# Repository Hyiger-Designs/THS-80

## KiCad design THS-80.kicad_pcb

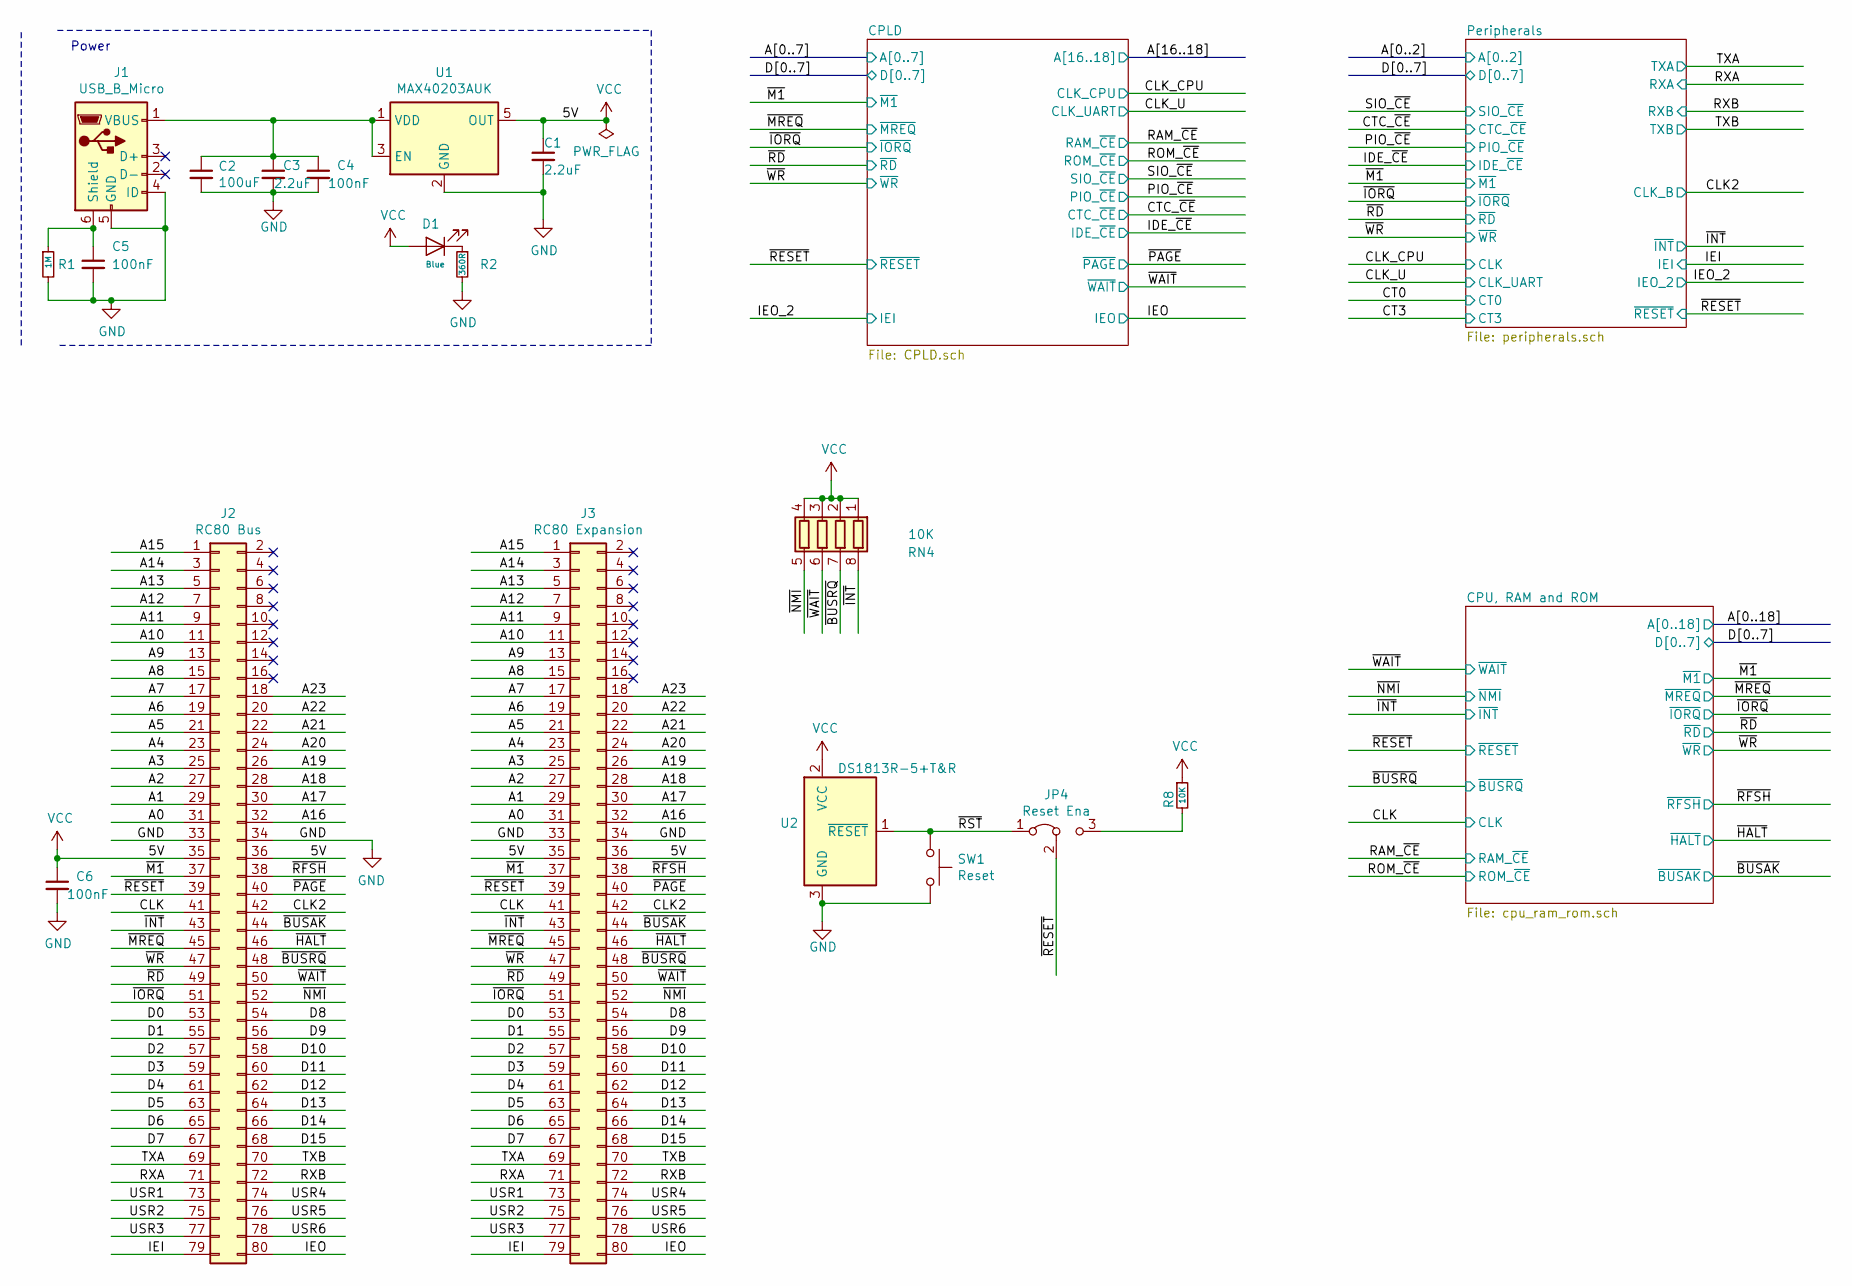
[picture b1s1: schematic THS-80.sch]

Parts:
C1, C3: 2.2uF; C_0603_1608Metric_Pad1.05x0.95mm_HandSolder; MPN C0805C105K4RACTU
C2: 100uF; C_1206_3216Metric_Pad1.42x1.75mm_HandSolder
C4, C5, C6: 100nF; C_0603_1608Metric_Pad1.05x0.95mm_HandSolder; MPN C0805C105K4RACTU
D1: Blue; LED_0603_1608Metric_Pad1.05x0.95mm_HandSolder
J1: USB_B_Micro; USB_Micro-B_Amphenol_10103594-0001LF_Horizontal; MPN 10103594-0001LF
J2: RC80 Bus; PinSocket_2x40_P2.54mm_Vertical
J3: RC80 Expansion; PinSocket_2x40_P2.54mm_Horizontal
JP4: Reset Ena; PinHeader_1x03_P2.54mm_Vertical
R1: 1M; R_0603_1608Metric_Pad1.05x0.95mm_HandSolder
R2: 360R; R_0603_1608Metric_Pad1.05x0.95mm_HandSolder
R8: 10K; R_0603_1608Metric_Pad1.05x0.95mm_HandSolder
RN4: 10K; R_Cat16-4
SW1: Reset; SW_SPST_FSMSM
U1: MAX40203AUK; SOT-23-5_HandSoldering; MPN MAX40203AUK+T; Mouser PN 700-MAX40203AUK+T
U2: DS1813R-5+T&R; SOT-23

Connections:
/A0: J2.31, J3.31; also elsewhere on the board
/A1: J2.29, J3.29; also elsewhere on the board
/A2: J2.27, J3.27; also elsewhere on the board
/A3: J2.25, J3.25; also elsewhere on the board
/A4: J2.23, J3.23; also elsewhere on the board
/A5: J2.21, J3.21; also elsewhere on the board
/A6: J2.19, J3.19; also elsewhere on the board
/A7: J2.17, J3.17; also elsewhere on the board
/A8: J2.15, J3.15; also elsewhere on the board
/A9: J2.13, J3.13; also elsewhere on the board
/A10: J2.11, J3.11; also elsewhere on the board
/A11: J2.9, J3.9; also elsewhere on the board
/A12: J2.7, J3.7; also elsewhere on the board
/A13: J2.5, J3.5; also elsewhere on the board
/A14: J2.3, J3.3; also elsewhere on the board
/A15: J2.1, J3.1; also elsewhere on the board
/A16: J2.32, J3.32; also elsewhere on the board
/A17: J2.30, J3.30; also elsewhere on the board
/A18: J2.28, J3.28; also elsewhere on the board
/A19: J2.26, J3.26
/A20: J2.24, J3.24
/A21: J2.22, J3.22
/A22: J2.20, J3.20
/A23: J2.18, J3.18
/CLK: J2.41, J3.41; also elsewhere on the board
/CLK2: J2.42, J3.42; also elsewhere on the board
/D0: J2.53, J3.53; also elsewhere on the board
/D1: J2.55, J3.55; also elsewhere on the board
/D2: J2.57, J3.57; also elsewhere on the board
/D3: J2.59, J3.59; also elsewhere on the board
/D4: J2.61, J3.61; also elsewhere on the board
/D5: J2.63, J3.63; also elsewhere on the board
/D6: J2.65, J3.65; also elsewhere on the board
/D7: J2.67, J3.67; also elsewhere on the board
/D8: J2.54, J3.54
/D9: J2.56, J3.56
/D10: J2.58, J3.58
/D11: J2.60, J3.60
/D12: J2.62, J3.62
/D13: J2.64, J3.64
/D14: J2.66, J3.66
/D15: J2.68, J3.68
/IEI: J2.79, J3.79; also elsewhere on the board
/IEO: J2.80, J3.80; also elsewhere on the board
/RXA: J2.71, J3.71; also elsewhere on the board
/RXB: J2.72, J3.72; also elsewhere on the board
/TXA: J2.69, J3.69; also elsewhere on the board
/TXB: J2.70, J3.70; also elsewhere on the board
/USR1: J2.73, J3.73
/USR2: J2.75, J3.75
/USR3: J2.77, J3.77
/USR4: J2.74, J3.74
/USR5: J2.76, J3.76
/USR6: J2.78, J3.78
/~BUSAK: J2.44, J3.44; also elsewhere on the board
/~BUSRQ: J2.48, J3.48, RN4.7 (R2.2); also elsewhere on the board
/~HALT: J2.46, J3.46; also elsewhere on the board
/~INT: J2.43, J3.43, RN4.8 (R1.2); also elsewhere on the board
/~IORQ: J2.51, J3.51; also elsewhere on the board
/~M1: J2.37, J3.37; also elsewhere on the board
/~MREQ: J2.45, J3.45; also elsewhere on the board
/~NMI: J2.52, J3.52, RN4.5 (R4.2); also elsewhere on the board
/~PAGE: J2.40, J3.40; also elsewhere on the board
/~RD: J2.49, J3.49; also elsewhere on the board
/~RESET: J2.39, J3.39, JP4.2 (C); also elsewhere on the board
/~RFSH: J2.38, J3.38; also elsewhere on the board
/~RST: JP4.1 (A), SW1.1, U2.1 (~RESET~)
/~WAIT: J2.50, J3.50, RN4.6 (R3.2); also elsewhere on the board
/~WR: J2.47, J3.47; also elsewhere on the board
GND: C1.2, C2.2, C3.2, C4.2, C5.2, C6.2, J1.4 (ID), J1.5 (GND), J2.33, J2.34, J3.33, J3.34, R1.2, R2.2, SW1.2, U1.2 (GND), U2.3 (GND); also elsewhere on the board
unnamed: C2.1, C3.1, C4.1, J1.1 (VBUS), U1.1 (VDD), U1.3 (EN)
unnamed: C5.1, J1.6 (Shield), R1.1
unnamed: D1.1 (K), R2.1
unnamed: JP4.3 (B), R8.2
VCC: C1.1, C6.1, D1.2 (A), J2.35, J2.36, J3.35, J3.36, R8.1, RN4.1 (R1.1), RN4.2 (R2.1), RN4.3 (R3.1), RN4.4 (R4.1), U1.5 (OUT), U2.2 (VCC); also elsewhere on the board

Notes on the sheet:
Power

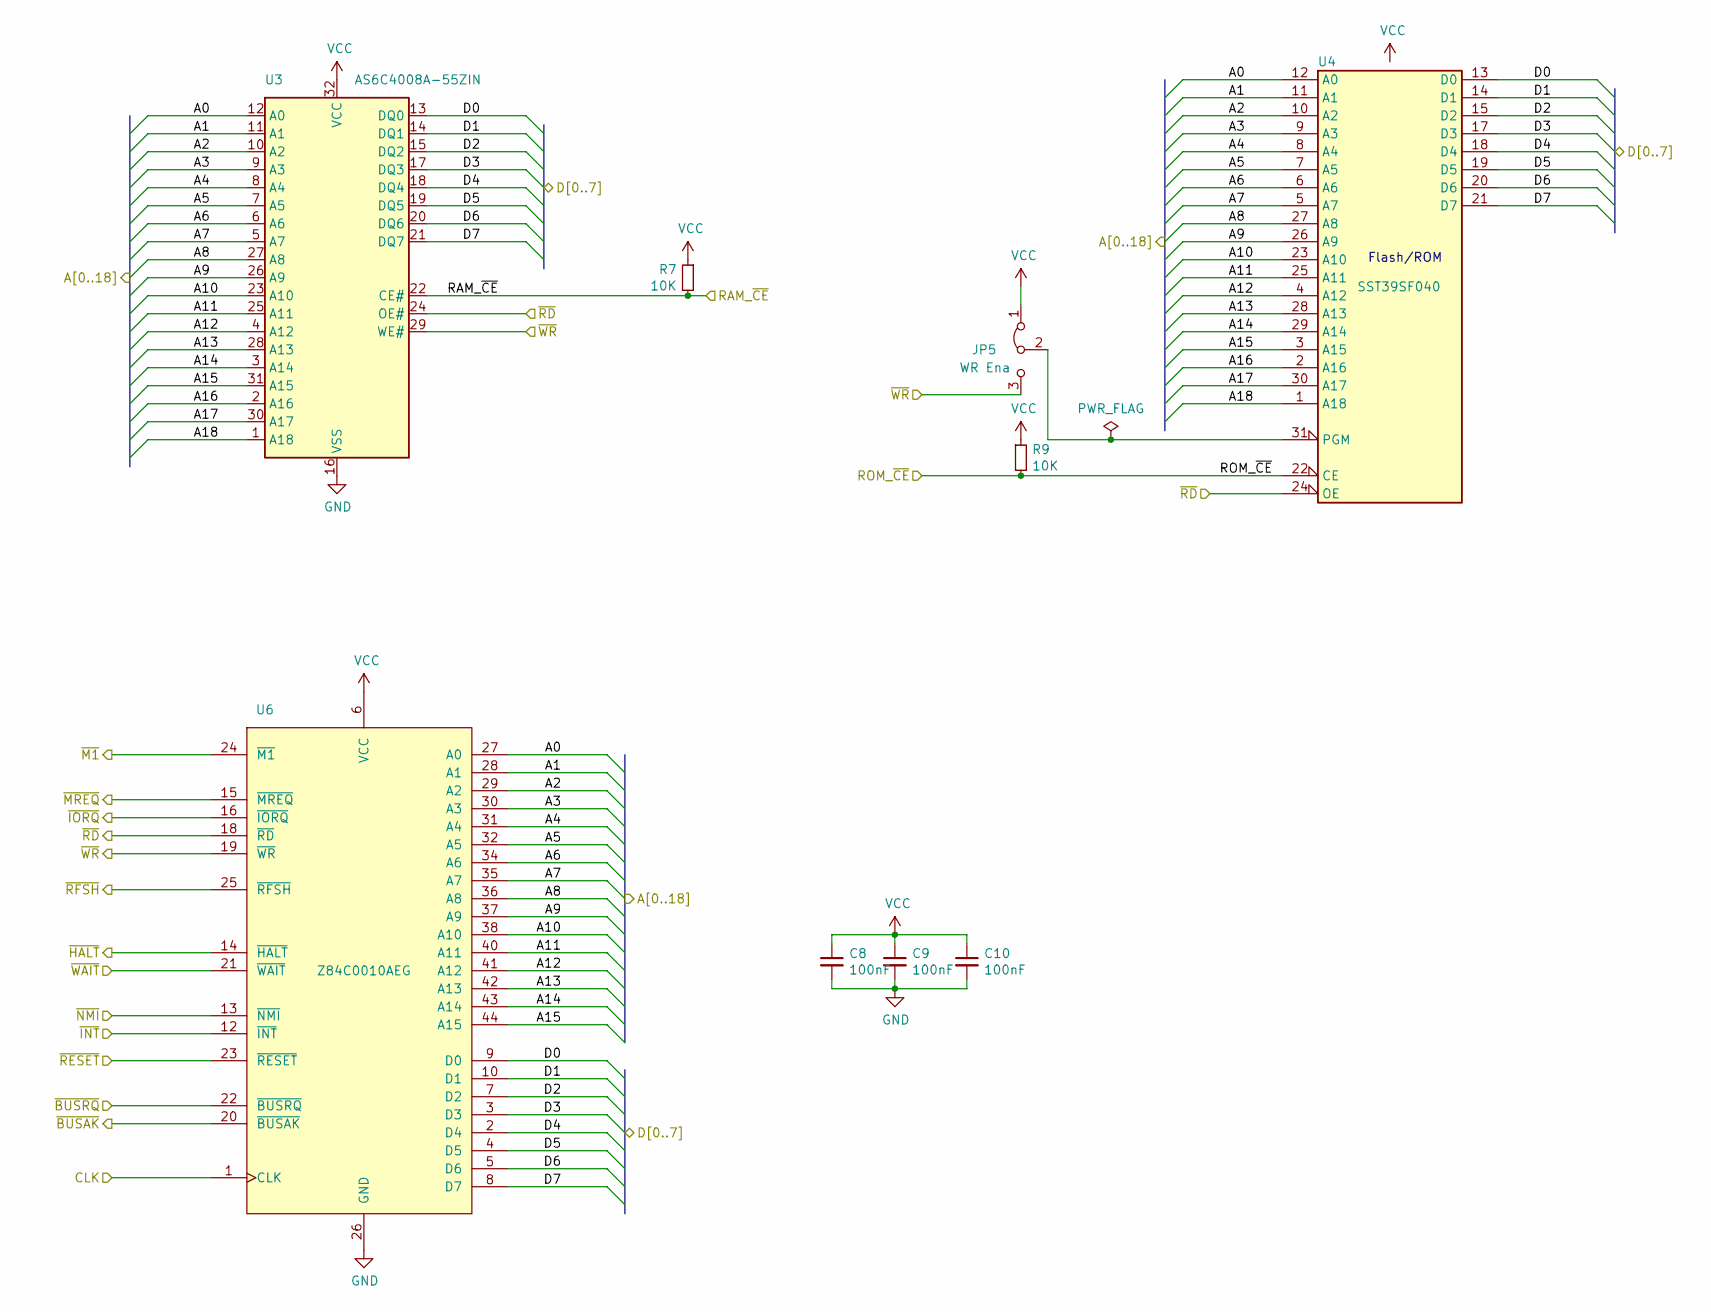
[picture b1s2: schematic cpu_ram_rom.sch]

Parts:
C8, C9, C10: 100nF; C_0603_1608Metric_Pad1.05x0.95mm_HandSolder
JP5: WR Ena; PinHeader_1x03_P2.54mm_Vertical
R7, R9: 10K; R_0603_1608Metric_Pad1.05x0.95mm_HandSolder
U3: AS6C4008A-55ZIN; TSOP-II-32_21.0x10.2mm_P1.27mm
U4: SST39SF040; PLCC-32_11.4x14.0mm_P1.27mm
U6: Z84C0010AEG; LQFP-44_10x10mm_P0.8mm; Manufacturer_Part_Number Z84C0010AEG

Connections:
/A0: U3.12 (A0), U4.12 (A0), U6.27 (A0); also elsewhere on the board
/A1: U3.11 (A1), U4.11 (A1), U6.28 (A1); also elsewhere on the board
/A2: U3.10 (A2), U4.10 (A2), U6.29 (A2); also elsewhere on the board
/A3: U3.9 (A3), U4.9 (A3), U6.30 (A3); also elsewhere on the board
/A4: U3.8 (A4), U4.8 (A4), U6.31 (A4); also elsewhere on the board
/A5: U3.7 (A5), U4.7 (A5), U6.32 (A5); also elsewhere on the board
/A6: U3.6 (A6), U4.6 (A6), U6.34 (A6); also elsewhere on the board
/A7: U3.5 (A7), U4.5 (A7), U6.35 (A7); also elsewhere on the board
/A8: U3.27 (A8), U4.27 (A8), U6.36 (A8); also elsewhere on the board
/A9: U3.26 (A9), U4.26 (A9), U6.37 (A9); also elsewhere on the board
/A10: U3.23 (A10), U4.23 (A10), U6.38 (A10); also elsewhere on the board
/A11: U3.25 (A11), U4.25 (A11), U6.40 (A11); also elsewhere on the board
/A12: U3.4 (A12), U4.4 (A12), U6.41 (A12); also elsewhere on the board
/A13: U3.28 (A13), U4.28 (A13), U6.42 (A13); also elsewhere on the board
/A14: U3.3 (A14), U4.29 (A14), U6.43 (A14); also elsewhere on the board
/A15: U3.31 (A15), U4.3 (A15), U6.44 (A15); also elsewhere on the board
/A16: U3.2 (A16), U4.2 (A16); also elsewhere on the board
/A17: U3.30 (A17), U4.30 (A17); also elsewhere on the board
/A18: U3.1 (A18), U4.1 (A18); also elsewhere on the board
/CLK: U6.1 (CLK); also elsewhere on the board
/D0: U3.13 (DQ0), U4.13 (D0), U6.9 (D0); also elsewhere on the board
/D1: U3.14 (DQ1), U4.14 (D1), U6.10 (D1); also elsewhere on the board
/D2: U3.15 (DQ2), U4.15 (D2), U6.7 (D2); also elsewhere on the board
/D3: U3.17 (DQ3), U4.17 (D3), U6.3 (D3); also elsewhere on the board
/D4: U3.18 (DQ4), U4.18 (D4), U6.2 (D4); also elsewhere on the board
/D5: U3.19 (DQ5), U4.19 (D5), U6.4 (D5); also elsewhere on the board
/D6: U3.20 (DQ6), U4.20 (D6), U6.5 (D6); also elsewhere on the board
/D7: U3.21 (DQ7), U4.21 (D7), U6.8 (D7); also elsewhere on the board
/RAM_~CE: R7.2, U3.22 (CE#); also elsewhere on the board
/ROM_~CE: R9.2, U4.22 (CE); also elsewhere on the board
/~BUSAK: U6.20 (~BUSAK); also elsewhere on the board
/~BUSRQ: U6.22 (~BUSRQ); also elsewhere on the board
/~HALT: U6.14 (~HALT); also elsewhere on the board
/~INT: U6.12 (~INT); also elsewhere on the board
/~IORQ: U6.16 (~IORQ); also elsewhere on the board
/~M1: U6.24 (~M1); also elsewhere on the board
/~MREQ: U6.15 (~MREQ); also elsewhere on the board
/~NMI: U6.13 (~NMI); also elsewhere on the board
/~RD: U3.24 (OE#), U4.24 (OE), U6.18 (~RD); also elsewhere on the board
/~RESET: U6.23 (~RESET); also elsewhere on the board
/~RFSH: U6.25 (~RFSH); also elsewhere on the board
/~WAIT: U6.21 (~WAIT); also elsewhere on the board
/~WR: JP5.3 (B), U3.29 (WE#), U6.19 (~WR); also elsewhere on the board
GND: C8.2, C9.2, C10.2, U3.16 (VSS), U4.16 (GND), U6.26 (GND); also elsewhere on the board
unnamed: JP5.2 (C), U4.31 (PGM)
VCC: C8.1, C9.1, C10.1, JP5.1 (A), R7.1, R9.1, U3.32 (VCC), U4.32 (VCC), U6.6 (VCC); also elsewhere on the board

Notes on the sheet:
Flash/ROM

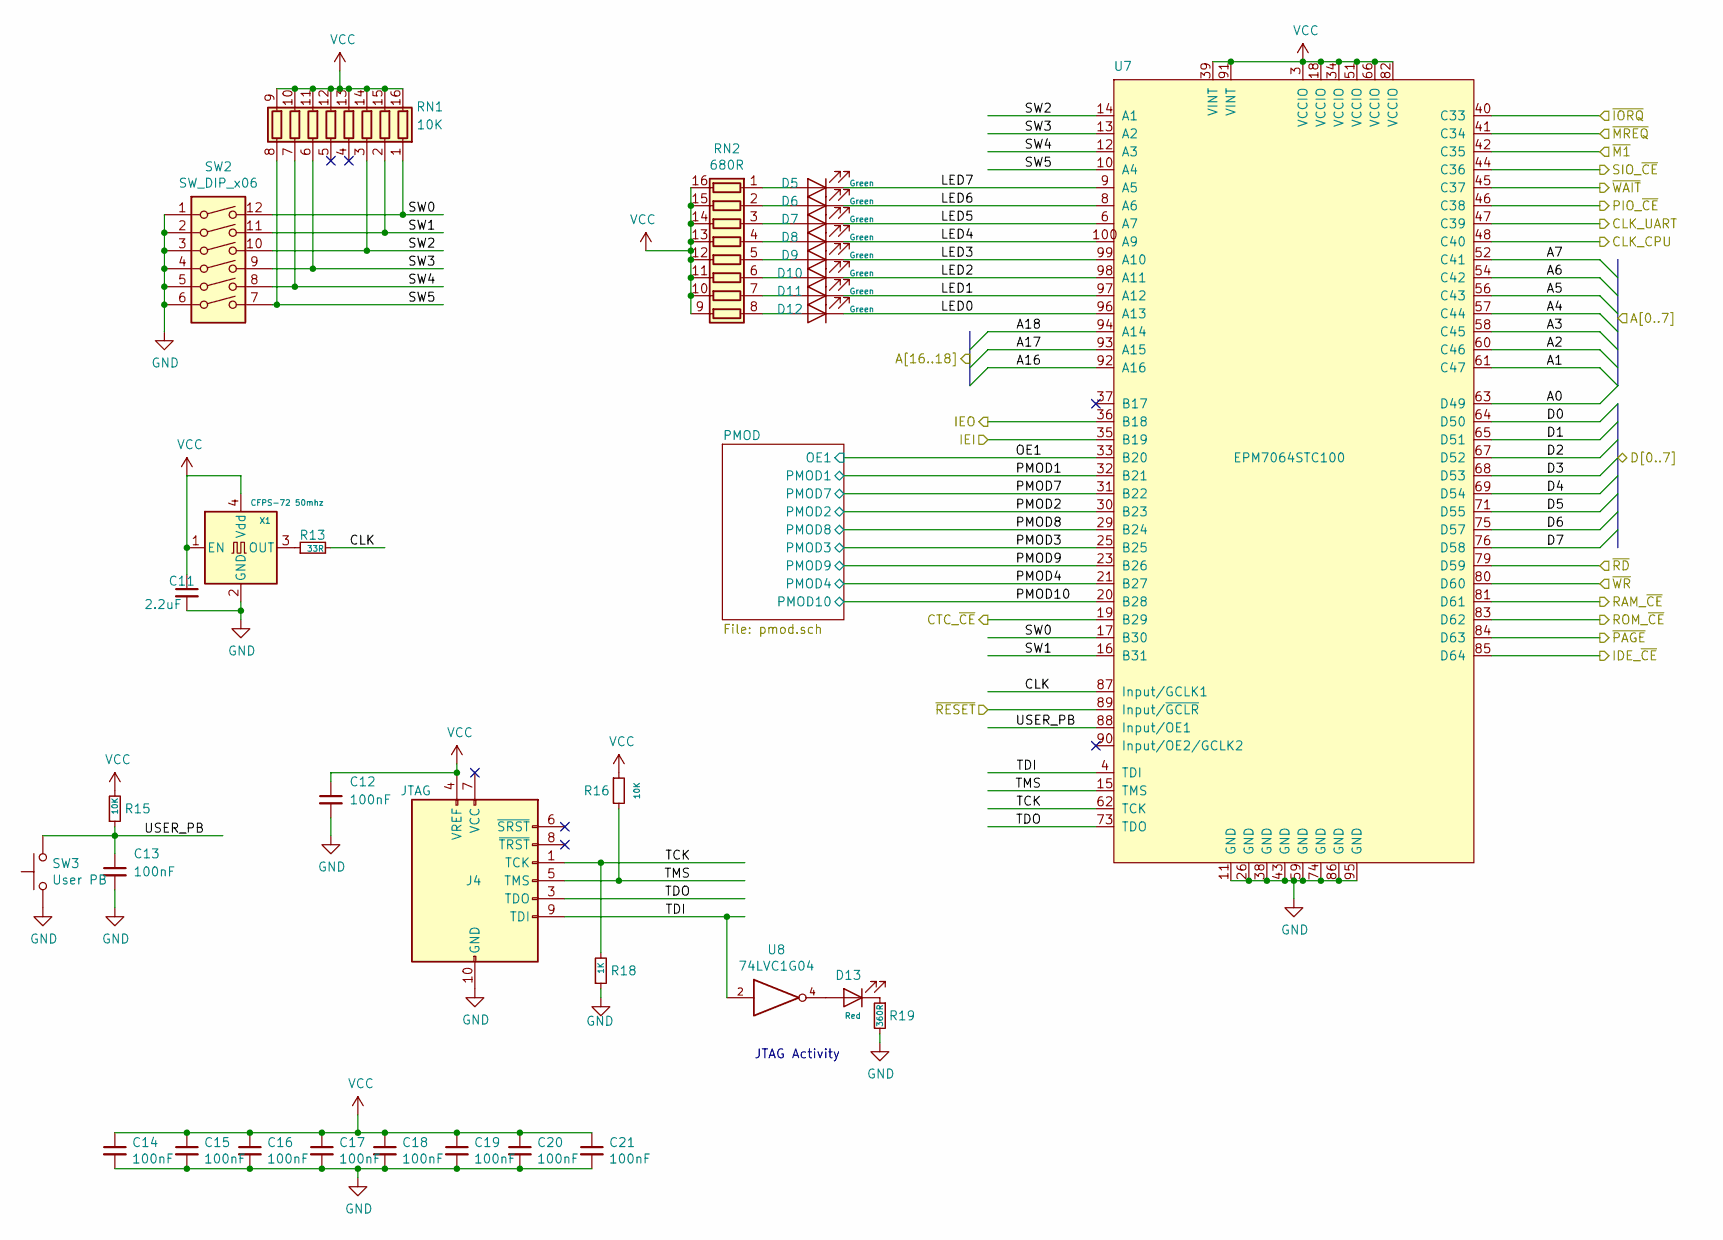
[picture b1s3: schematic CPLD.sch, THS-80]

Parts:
C11: 2.2uF; C_0603_1608Metric_Pad1.05x0.95mm_HandSolder; MPN JMK107B7474KA-T
C12, C13: 100nF; C_0603_1608Metric_Pad1.05x0.95mm_HandSolder; MPN JMK107B7474KA-T
C14, C15, C16, C17, C18, C19, C20, C21: 100nF; C_0603_1608Metric_Pad1.05x0.95mm_HandSolder
D5, D6, D7, D8, D9, D10, D11, D12: Green; LED_0603_1608Metric_Pad1.05x0.95mm_HandSolder
D13: Red; LED_0603_1608Metric_Pad1.05x0.95mm_HandSolder
J4: JTAG; Multicomp_MC9A12-1034_2x05_P2.54mm_Vertical
R13: 33R; R_0603_1608Metric_Pad1.05x0.95mm_HandSolder
R15, R16: 10K; R_0603_1608Metric_Pad1.05x0.95mm_HandSolder
R18: 1K; R_0603_1608Metric_Pad1.05x0.95mm_HandSolder
R19: 360R; R_0603_1608Metric_Pad1.05x0.95mm_HandSolder
RN1: 10K; R_Cat16-8
RN2: 680R; R_Cat16-8
SW2: SW_DIP_x06; SW_DIP_SPSTx06_Slide_Omron_A6S-610x_W8.9mm_P2.54mm
SW3: User PB; SW_SPST_FSMSM
U7: EPM7064STC100; TQFP-100_14x14mm_P0.5mm
U8: 74LVC1G04; TSOP-5_1.65x3.05mm_P0.95mm
X1: CFPS-72 50mhz; Oscillator_SMD_SeikoEpson_SG8002CA-4Pin_7.0x5.0mm_HandSolde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

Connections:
/A0: U7.63 (D49); also elsewhere on the board
/A1: U7.61 (C47); also elsewhere on the board
/A2: U7.60 (C46); also elsewhere on the board
/A3: U7.58 (C45); also elsewhere on the board
/A4: U7.57 (C44); also elsewhere on the board
/A5: U7.56 (C43); also elsewhere on the board
/A6: U7.54 (C42); also elsewhere on the board
/A7: U7.52 (C41); also elsewhere on the board
/A16: U7.92 (A16); also elsewhere on the board
/A17: U7.93 (A15); also elsewhere on the board
/A18: U7.94 (A14); also elsewhere on the board
/CLK_CPU: U7.48 (C40); also elsewhere on the board
/CLK_U: U7.47 (C39); also elsewhere on the board
/CPLD/CLK: R13.2, U7.87 (Input/GCLK1)
/CPLD/LED0: D12.1 (K), U7.96 (A13)
/CPLD/LED1: D11.1 (K), U7.97 (A12)
/CPLD/LED2: D10.1 (K), U7.98 (A11)
/CPLD/LED3: D9.1 (K), U7.99 (A10)
/CPLD/LED4: D8.1 (K), U7.100 (A9)
/CPLD/LED5: D7.1 (K), U7.6 (A7)
/CPLD/LED6: D6.1 (K), U7.8 (A6)
/CPLD/LED7: D5.1 (K), U7.9 (A5)
/CPLD/OE1: U7.33 (B20); also elsewhere on the board
/CPLD/PMOD1: U7.32 (B21); also elsewhere on the board
/CPLD/PMOD2: U7.30 (B23); also elsewhere on the board
/CPLD/PMOD3: U7.25 (B25); also elsewhere on the board
/CPLD/PMOD4: U7.21 (B27); also elsewhere on the board
/CPLD/PMOD7: U7.31 (B22); also elsewhere on the board
/CPLD/PMOD8: U7.29 (B24); also elsewhere on the board
/CPLD/PMOD9: U7.23 (B26); also elsewhere on the board
/CPLD/PMOD10: U7.20 (B28); also elsewhere on the board
/CPLD/SW0: RN1.1 (R1.1), SW2.12, U7.17 (B30)
/CPLD/SW1: RN1.2 (R2.1), SW2.11, U7.16 (B31)
/CPLD/SW2: RN1.3 (R3.1), SW2.10, U7.14 (A1)
/CPLD/SW3: RN1.6 (R6.1), SW2.9, U7.13 (A2)
/CPLD/SW4: RN1.7 (R7.1), SW2.8, U7.12 (A3)
/CPLD/SW5: RN1.8 (R8.1), SW2.7, U7.10 (A4)
/CPLD/TCK: J4.1 (TCK), R18.2, U7.62 (TCK)
/CPLD/TDI: J4.9 (TDI), U7.4 (TDI), U8.2
/CPLD/TDO: J4.3 (TDO), U7.73 (TDO)
/CPLD/TMS: J4.5 (TMS), R16.2, U7.15 (TMS)
/CPLD/USER_PB: C13.1, R15.1, SW3.2, U7.88 (Input/OE1)
/CTC_~CE: U7.19 (B29); also elsewhere on the board
/D0: U7.64 (D50); also elsewhere on the board
/D1: U7.65 (D51); also elsewhere on the board
/D2: U7.67 (D52); also elsewhere on the board
/D3: U7.68 (D53); also elsewhere on the board
/D4: U7.69 (D54); also elsewhere on the board
/D5: U7.71 (D55); also elsewhere on the board
/D6: U7.75 (D57); also elsewhere on the board
/D7: U7.76 (D58); also elsewhere on the board
/IDE_~CE~: U7.85 (D64); also elsewhere on the board
/IEO: U7.36 (B18); also elsewhere on the board
/IEO_2: U7.35 (B19); also elsewhere on the board
/PIO_~CE: U7.46 (C38); also elsewhere on the board
/RAM_~CE: U7.81 (D61); also elsewhere on the board
/ROM_~CE: U7.83 (D62); also elsewhere on the board
/SIO_~CE: U7.44 (C36); also elsewhere on the board
/~IORQ: U7.40 (C33); also elsewhere on the board
/~M1: U7.42 (C35); also elsewhere on the board
/~MREQ: U7.41 (C34); also elsewhere on the board
/~PAGE: U7.84 (D63); also elsewhere on the board
/~RD: U7.79 (D59); also elsewhere on the board
/~RESET: U7.89 (Input/~GCLR); also elsewhere on the board
/~WAIT: U7.45 (C37); also elsewhere on the board
/~WR: U7.80 (D60); also elsewhere on the board
GND: C11.2, C12.2, C13.2, C14.2, C15.2, C16.2, C17.2, C18.2, C19.2, C20.2, C21.2, J4.2 (GND), J4.10 (GND), R18.1, R19.2, SW2.1, SW2.2, SW2.3, SW2.4, SW2.5, SW2.6, SW3.1, U7.11 (GND), U7.26 (GND), U7.38 (GND), U7.43 (GND), U7.59 (GND), U7.74 (GND), U7.86 (GND), U7.95 (GND), U8.3 (GND), X1.2 (GND); also elsewhere on the board
unnamed: D5.2 (A), RN2.1 (R1.1)
unnamed: D6.2 (A), RN2.2 (R2.1)
unnamed: D7.2 (A), RN2.3 (R3.1)
unnamed: D8.2 (A), RN2.4 (R4.1)
unnamed: D9.2 (A), RN2.5 (R5.1)
unnamed: D10.2 (A), RN2.6 (R6.1)
unnamed: D11.2 (A), RN2.7 (R7.1)
unnamed: D12.2 (A), RN2.8 (R8.1)
unnamed: D13.1 (K), R19.1
unnamed: D13.2 (A), U8.4
unnamed: R13.1, X1.3 (OUT)
VCC: C11.1, C12.1, C14.1, C15.1, C16.1, C17.1, C18.1, C19.1, C20.1, C21.1, J4.4 (VREF), R15.2, R16.1, RN1.9 (R8.2), RN1.10 (R7.2), RN1.11 (R6.2), RN1.12 (R5.2), RN1.13 (R4.2), RN1.14 (R3.2), RN1.15 (R2.2), RN1.16 (R1.2), RN2.9 (R8.2), RN2.10 (R7.2), RN2.11 (R6.2), RN2.12 (R5.2), RN2.13 (R4.2), RN2.14 (R3.2), RN2.15 (R2.2), RN2.16 (R1.2), U7.3 (VCCIO), U7.18 (VCCIO), U7.34 (VCCIO), U7.39 (VINT), U7.51 (VCCIO), U7.66 (VCCIO), U7.82 (VCCIO), U7.91 (VINT), U8.5 (VCC), X1.1 (EN), X1.4 (Vdd); also elsewhere on the board

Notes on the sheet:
JTAG Activity

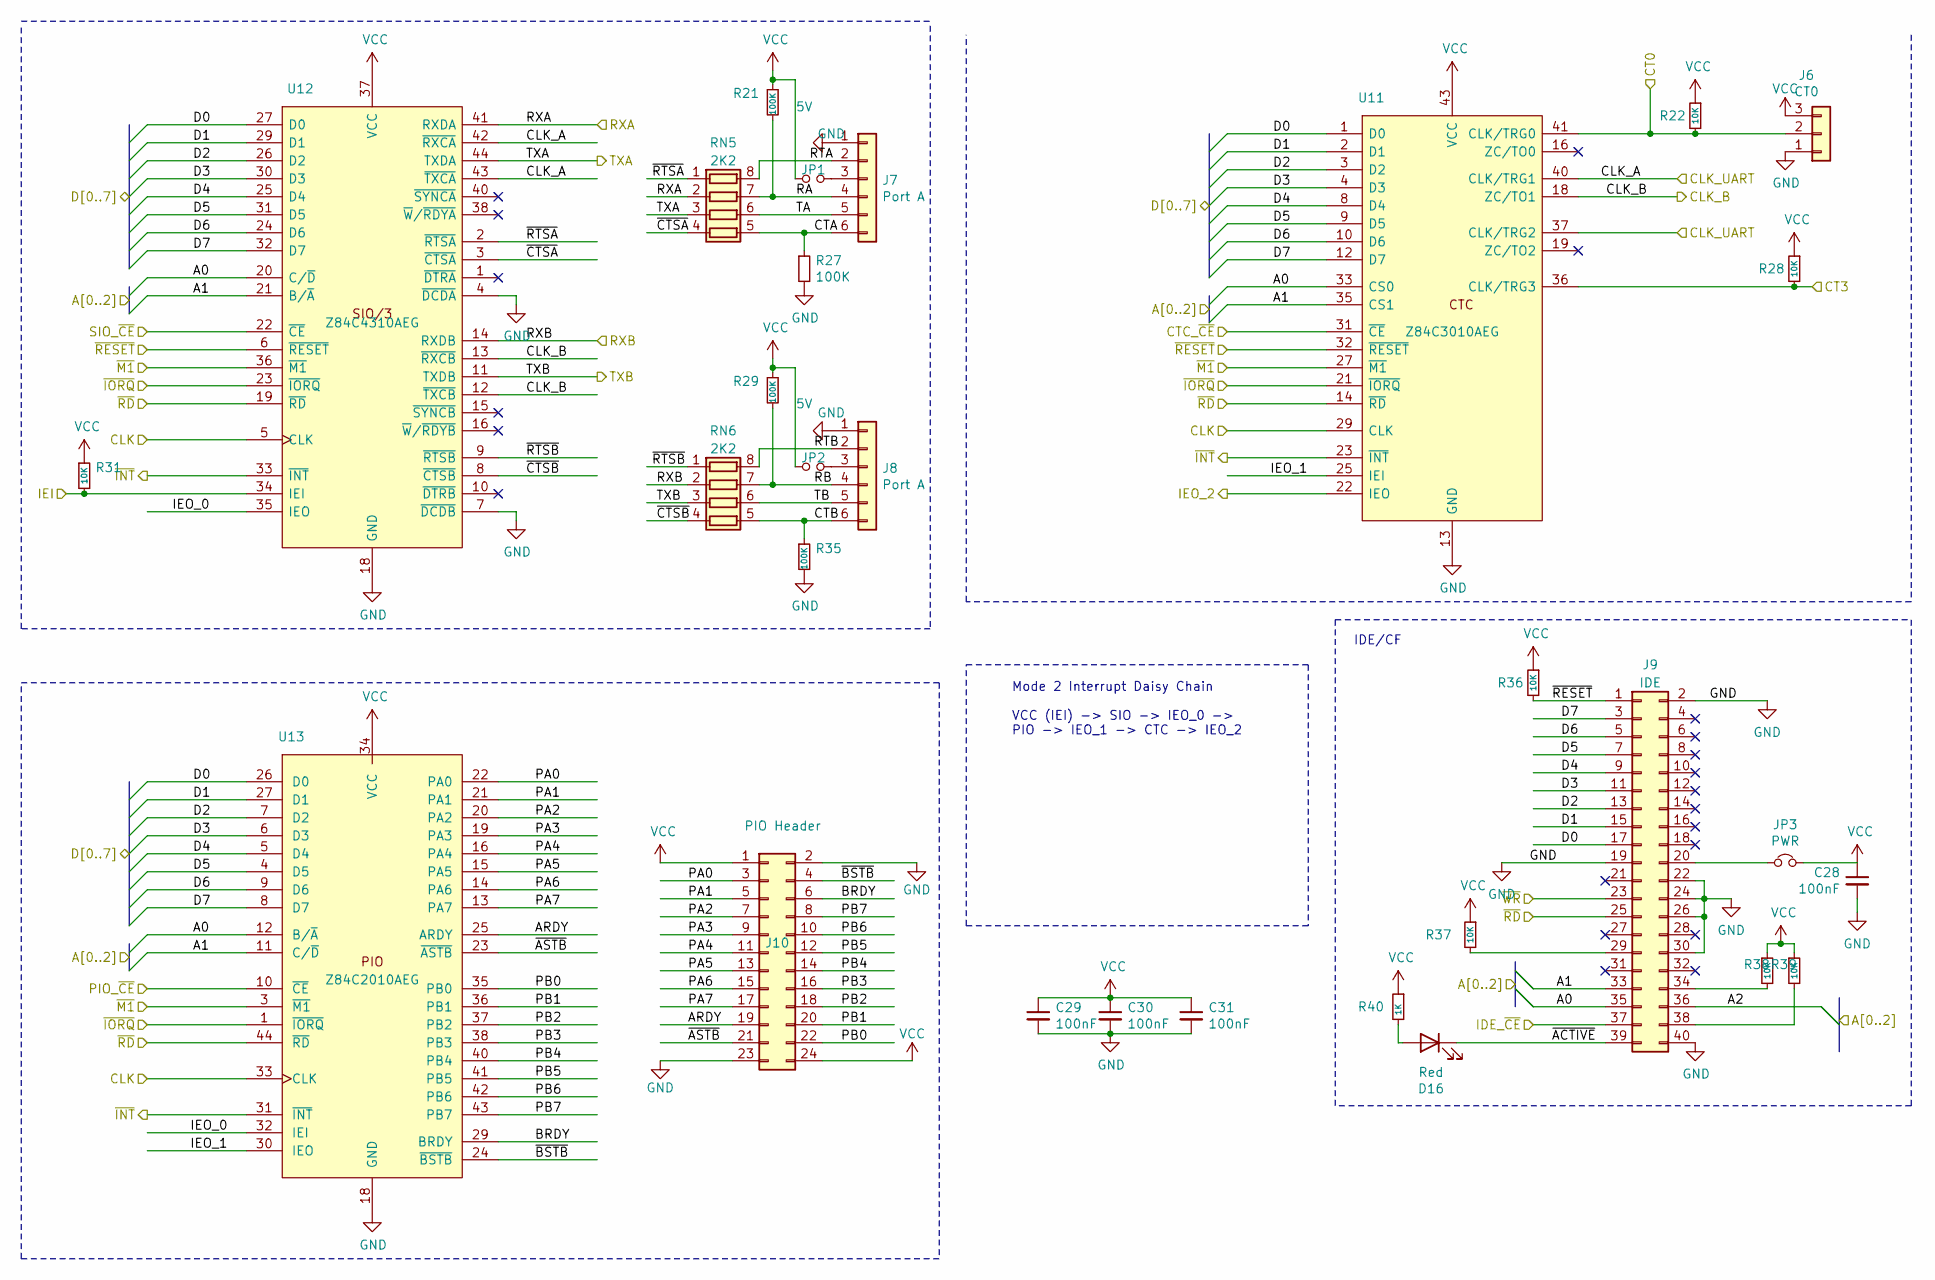
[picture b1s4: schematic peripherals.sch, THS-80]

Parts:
C28, C29, C30, C31: 100nF; C_0603_1608Metric_Pad1.05x0.95mm_HandSolder; MPN JMK107B7474KA-T
D16: Red; LED_0603_1608Metric_Pad1.05x0.95mm_HandSolder
J6: CT0; PinHeader_1x03_P2.54mm_Horizontal
J7, J8: Port A; PinHeader_1x06_P2.54mm_Horizontal
J9: IDE; PinHeader_2x20_P2.54mm_Horizontal
J10: PIO Header; PinHeader_2x12_P2.54mm_Horizontal
JP1, JP2: 5V; PinHeader_1x02_P2.54mm_Vertical
JP3: PWR; PinHeader_1x02_P2.54mm_Vertical
R21, R27, R29, R35: 100K; R_0603_1608Metric_Pad1.05x0.95mm_HandSolder
R22, R28, R31, R36, R37, R38, R39: 10K; R_0603_1608Metric_Pad1.05x0.95mm_HandSolder
R40: 1K; R_0603_1608Metric_Pad1.05x0.95mm_HandSolder
RN5, RN6: 2K2; R_Cat16-4
U11: Z84C3010AEG; LQFP-44_10x10mm_P0.8mm; Manufacturer_Part_Number Z84C4310AEG
U12: Z84C4310AEG; LQFP-44_10x10mm_P0.8mm; Manufacturer_Part_Number Z84C4310AEG
U13: Z84C2010AEG; LQFP-44_10x10mm_P0.8mm; Manufacturer_Part_Number Z84C2010AEG

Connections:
/A0: J9.35, U11.33 (CS0), U12.20 (C/~D), U13.12 (B/~A); also elsewhere on the board
/A1: J9.33, U11.35 (CS1), U12.21 (B/~A), U13.11 (C/~D); also elsewhere on the board
/A2: J9.36; also elsewhere on the board
/CLK2: U11.18 (ZC/TO1), U12.12 (~TXCB), U12.13 (~RXCB); also elsewhere on the board
/CLK_CPU: U11.29 (CLK), U12.5 (CLK), U13.33 (CLK); also elsewhere on the board
/CLK_U: U11.37 (CLK/TRG2), U11.40 (CLK/TRG1), U12.42 (~RXCA), U12.43 (~TXCA); also elsewhere on the board
/CT0: J6.2, R22.2, U11.41 (CLK/TRG0)
/CT3: R28.2, U11.36 (CLK/TRG3)
/CTC_~CE: U11.31 (~CE); also elsewhere on the board
/D0: J9.17, U11.1 (D0), U12.27 (D0), U13.26 (D0); also elsewhere on the board
/D1: J9.15, U11.2 (D1), U12.29 (D1), U13.27 (D1); also elsewhere on the board
/D2: J9.13, U11.3 (D2), U12.26 (D2), U13.7 (D2); also elsewhere on the board
/D3: J9.11, U11.4 (D3), U12.30 (D3), U13.6 (D3); also elsewhere on the board
/D4: J9.9, U11.8 (D4), U12.25 (D4), U13.5 (D4); also elsewhere on the board
/D5: J9.7, U11.9 (D5), U12.31 (D5), U13.4 (D5); also elsewhere on the board
/D6: J9.5, U11.10 (D6), U12.24 (D6), U13.9 (D6); also elsewhere on the board
/D7: J9.3, U11.12 (D7), U12.32 (D7), U13.8 (D7); also elsewhere on the board
/IDE_~CE~: J9.37; also elsewhere on the board
/IEI: R31.2, U12.34 (IEI); also elsewhere on the board
/IEO_2: U11.22 (IEO); also elsewhere on the board
/PIO_~CE: U13.10 (~CE); also elsewhere on the board
/Peripherals/ARDY: J10.19, U13.25 (ARDY)
/Peripherals/BRDY: J10.6, U13.29 (BRDY)
/Peripherals/CTA: J7.6, R27.1, RN5.5 (R4.2)
/Peripherals/CTB: J8.6, R35.1, RN6.5 (R4.2)
/Peripherals/IEO_0: U12.35 (IEO), U13.32 (IEI)
/Peripherals/IEO_1: U11.25 (IEI), U13.30 (IEO)
/Peripherals/PA0: J10.3, U13.22 (PA0)
/Peripherals/PA1: J10.5, U13.21 (PA1)
/Peripherals/PA2: J10.7, U13.20 (PA2)
/Peripherals/PA3: J10.9, U13.19 (PA3)
/Peripherals/PA4: J10.11, U13.16 (PA4)
/Peripherals/PA5: J10.13, U13.15 (PA5)
/Peripherals/PA6: J10.15, U13.14 (PA6)
/Peripherals/PA7: J10.17, U13.13 (PA7)
/Peripherals/PB0: J10.22, U13.35 (PB0)
/Peripherals/PB1: J10.20, U13.36 (PB1)
/Peripherals/PB2: J10.18, U13.37 (PB2)
/Peripherals/PB3: J10.16, U13.38 (PB3)
/Peripherals/PB4: J10.14, U13.40 (PB4)
/Peripherals/PB5: J10.12, U13.41 (PB5)
/Peripherals/PB6: J10.10, U13.42 (PB6)
/Peripherals/PB7: J10.8, U13.43 (PB7)
/Peripherals/RA: J7.4, R21.2, RN5.7 (R2.2)
/Peripherals/RB: J8.4, R29.2, RN6.7 (R2.2)
/Peripherals/RTA: J7.2, RN5.8 (R1.2)
/Peripherals/RTB: J8.2, RN6.8 (R1.2)
/Peripherals/TA: J7.5, RN5.6 (R3.2)
/Peripherals/TB: J8.5, RN6.6 (R3.2)
/Peripherals/~ACTIVE: D16.1 (K), J9.39
/Peripherals/~ASTB: J10.21, U13.23 (~ASTB)
/Peripherals/~BSTB: J10.4, U13.24 (~BSTB)
/Peripherals/~CTSA: RN5.4 (R4.1), U12.3 (~CTSA)
/Peripherals/~CTSB: RN6.4 (R4.1), U12.8 (~CTSB)
/Peripherals/~RESET: J9.1, R36.2
/Peripherals/~RTSA: RN5.1 (R1.1), U12.2 (~RTSA)
/Peripherals/~RTSB: RN6.1 (R1.1), U12.9 (~RTSB)
/RXA: RN5.2 (R2.1), U12.41 (RXDA); also elsewhere on the board
/RXB: RN6.2 (R2.1), U12.14 (RXDB); also elsewhere on the board
/SIO_~CE: U12.22 (~CE); also elsewhere on the board
/TXA: RN5.3 (R3.1), U12.44 (TXDA); also elsewhere on the board
/TXB: RN6.3 (R3.1), U12.11 (TXDB); also elsewhere on the board
/~INT: U11.23 (~INT), U12.33 (~INT), U13.31 (~INT); also elsewhere on the board
/~IORQ: U11.21 (~IORQ), U12.23 (~IORQ), U13.1 (~IORQ); also elsewhere on the board
/~M1: U11.27 (~M1), U12.36 (~M1), U13.3 (~M1); also elsewhere on the board
/~RD: J9.25, U11.14 (~RD), U12.19 (~RD), U13.44 (~RD); also elsewhere on the board
/~RESET: U11.32 (~RESET), U12.6 (~RESET); also elsewhere on the board
/~WR: J9.23; also elsewhere on the board
GND: C28.2, C29.2, C30.2, C31.2, J6.1, J7.1, J8.1, J9.2, J9.19, J9.22, J9.24, J9.26, J9.30, J9.40, J10.2, J10.23, R27.2, R35.2, U11.13 (GND), U12.4 (~DCDA), U12.7 (~DCDB), U12.18 (GND), U13.18 (GND); also elsewhere on the board
unnamed: D16.2 (A), R40.2
unnamed: J7.3, JP1.2
unnamed: J8.3, JP2.2
unnamed: J9.20, JP3.1
unnamed: J9.29, R37.2
unnamed: J9.34, R38.2
unnamed: J9.38, R39.2
VCC: C28.1, C29.1, C30.1, C31.1, J6.3, J10.1, J10.24, JP1.1, JP2.1, JP3.2, R21.1, R22.1, R28.1, R29.1, R31.1, R36.1, R37.1, R38.1, R39.1, R40.1, U11.43 (VCC), U12.37 (VCC), U13.34 (VCC); also elsewhere on the board

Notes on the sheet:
IDE/CF
Mode 2 Interrupt Daisy Chain VCC (IEI) -> SIO -> IEO_0 -> PIO -> IEO_1 -> CTC -> IEO_2

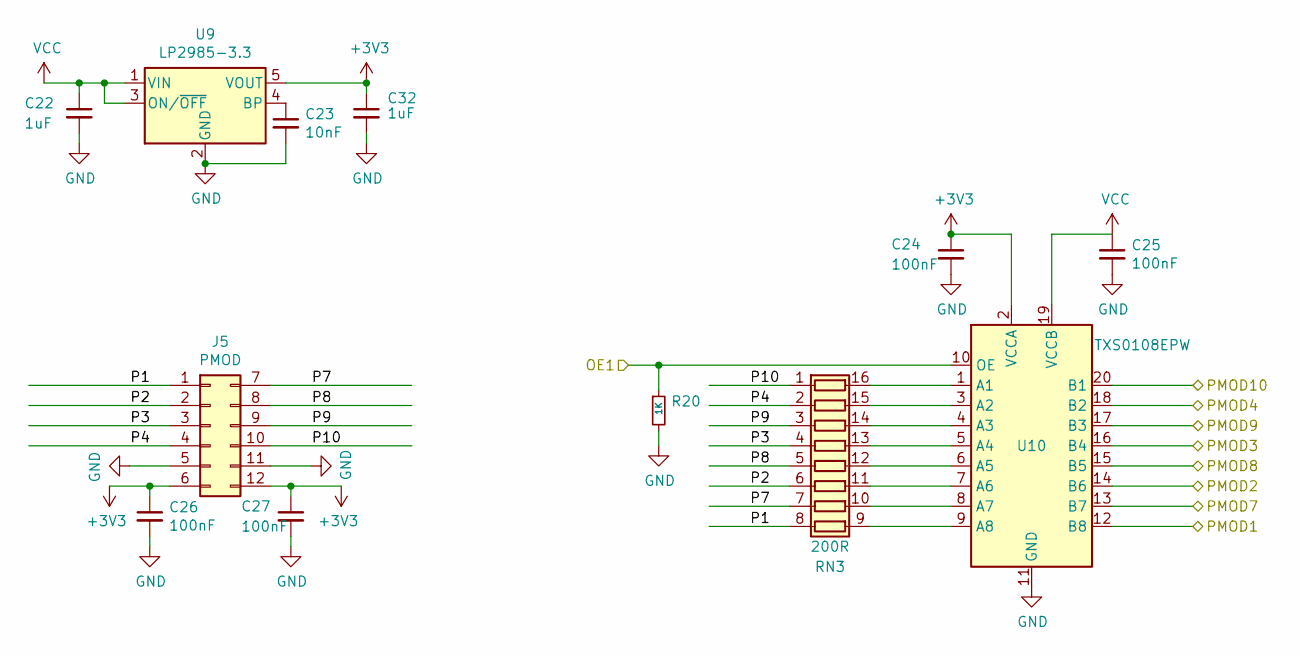
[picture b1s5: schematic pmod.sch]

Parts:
C22, C32: 1uF; C_0603_1608Metric_Pad1.05x0.95mm_HandSolder
C23: 10nF; C_0603_1608Metric_Pad1.05x0.95mm_HandSolder
C24, C25, C26, C27: 100nF; C_0603_1608Metric_Pad1.05x0.95mm_HandSolder
J5: PMOD; PinSocket_2x06_P2.54mm_Horizontal
R20: 1K; R_0603_1608Metric_Pad1.05x0.95mm_HandSolder
RN3: 200R; R_Cat16-8
U9: LP2985-3.3; SOT-23-5
U10: TXS0108EPW; TSSOP-20_4.4x6.5mm_P0.65mm

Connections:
+3V3: C24.1, C26.1, C27.1, C32.1, J5.6, J5.12, U9.5 (VOUT), U10.2 (VCCA)
/CPLD/OE1: R20.1, U10.10 (OE); also elsewhere on the board
/CPLD/PMOD1: U10.12 (B8); also elsewhere on the board
/CPLD/PMOD2: U10.14 (B6); also elsewhere on the board
/CPLD/PMOD3: U10.16 (B4); also elsewhere on the board
/CPLD/PMOD4: U10.18 (B2); also elsewhere on the board
/CPLD/PMOD7: U10.13 (B7); also elsewhere on the board
/CPLD/PMOD8: U10.15 (B5); also elsewhere on the board
/CPLD/PMOD9: U10.17 (B3); also elsewhere on the board
/CPLD/PMOD10: U10.20 (B1); also elsewhere on the board
/CPLD/PMOD/P1: J5.1, RN3.8 (R8.1)
/CPLD/PMOD/P2: J5.2, RN3.6 (R6.1)
/CPLD/PMOD/P3: J5.3, RN3.4 (R4.1)
/CPLD/PMOD/P4: J5.4, RN3.2 (R2.1)
/CPLD/PMOD/P7: J5.7, RN3.7 (R7.1)
/CPLD/PMOD/P8: J5.8, RN3.5 (R5.1)
/CPLD/PMOD/P9: J5.9, RN3.3 (R3.1)
/CPLD/PMOD/P10: J5.10, RN3.1 (R1.1)
GND: C22.2, C23.2, C24.2, C25.2, C26.2, C27.2, C32.2, J5.5, J5.11, R20.2, U9.2 (GND), U10.11 (GND); also elsewhere on the board
unnamed: C23.1, U9.4 (BP)
unnamed: RN3.9 (R8.2), U10.9 (A8)
unnamed: RN3.10 (R7.2), U10.8 (A7)
unnamed: RN3.11 (R6.2), U10.7 (A6)
unnamed: RN3.12 (R5.2), U10.6 (A5)
unnamed: RN3.13 (R4.2), U10.5 (A4)
unnamed: RN3.14 (R3.2), U10.4 (A3)
unnamed: RN3.15 (R2.2), U10.3 (A2)
unnamed: RN3.16 (R1.2), U10.1 (A1)
VCC: C22.1, C25.1, U9.1 (VIN), U9.3 (ON/~OFF~), U10.19 (VCCB); also elsewhere on the board
